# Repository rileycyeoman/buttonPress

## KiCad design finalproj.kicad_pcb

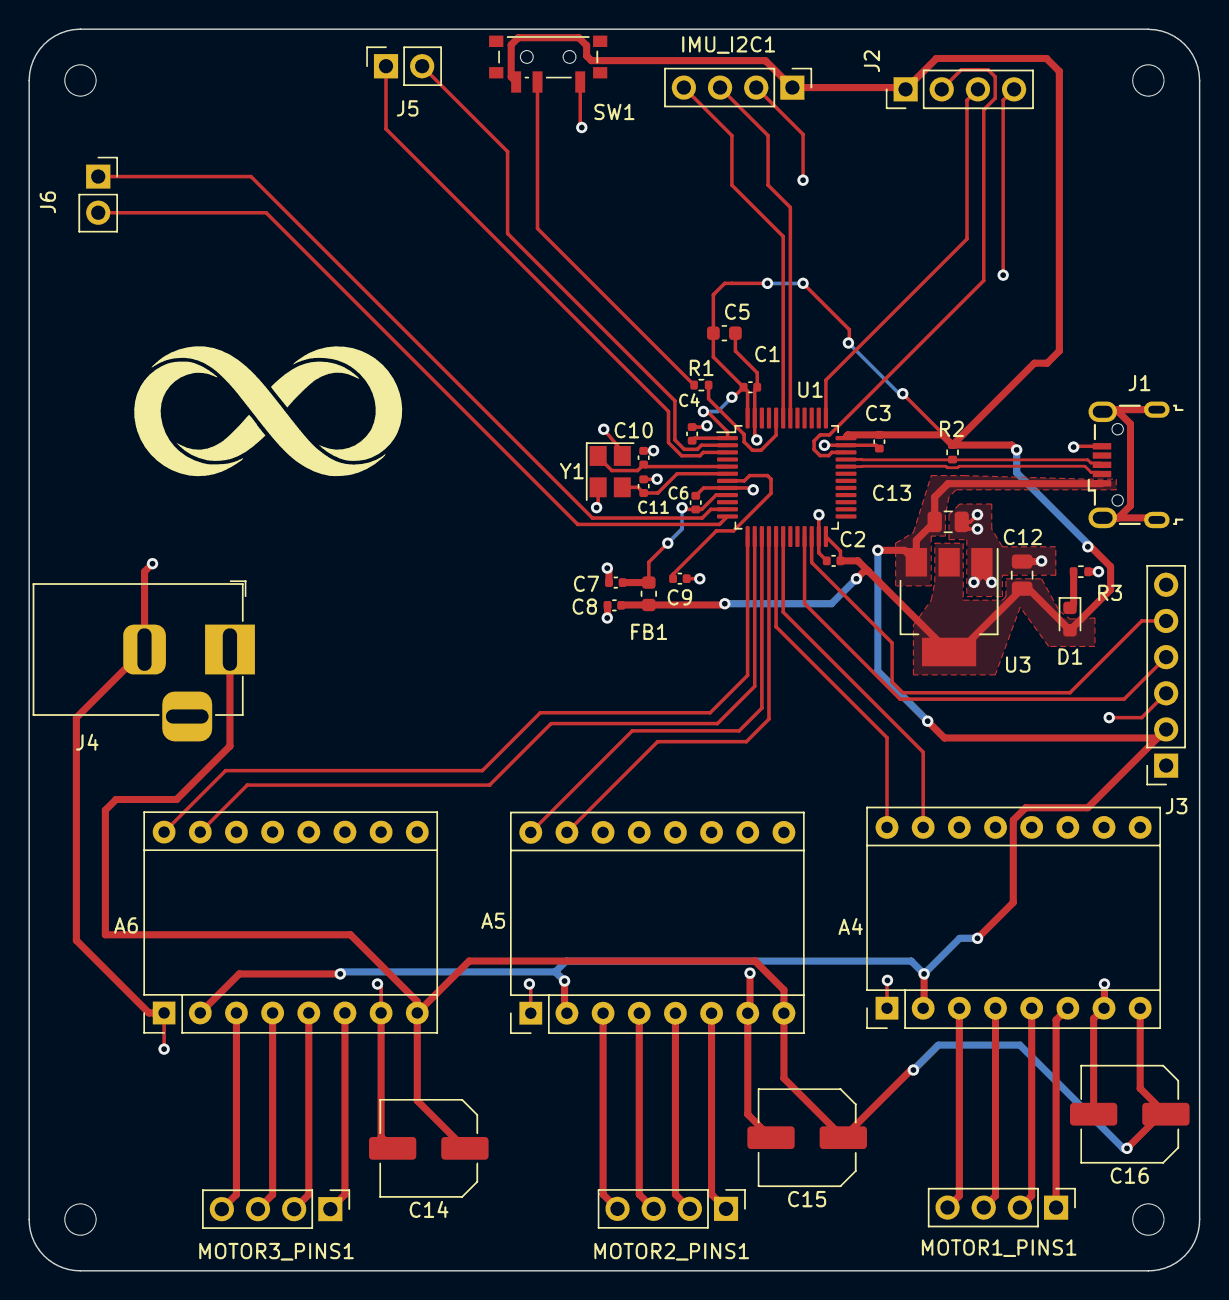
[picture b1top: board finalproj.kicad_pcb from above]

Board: 2 copper layers, 82.2 x 87.2 mm, 43 parts (0 on the bottom side), 41 nets.

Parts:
A4, A5, A6: Pololu_Breakout_A4988; Pololu_Breakout-16_15.2x20.3mm
C1, C2, C3, C4, C9: 100nF; C_0402_1005Metric
C5: 10uF; C_0603_1608Metric
C6: 10nF; C_0402_1005Metric
C7, C8: 1uF; C_0402_1005Metric
C10, C11: 10pF; C_0402_1005Metric
C12, C13: 22uF; C_0805_2012Metric
C14, C15, C16: 47uF; C_Elec_6.3x5.8
D1: LED; LED_0603_1608Metric
FB1: 120R; L_0603_1608Metric
H1, H2, H3, H4: MountingHole; MountingHole_2.2mm_M2
IMU_I2C1: Conn_01x04_Pin; PinHeader_1x04_P2.54mm_Vertical
J1: USB_B_Micro; USB_Micro-B_Wuerth_629105150521
J2: Conn_01x04_Pin; PinHeader_1x04_P2.54mm_Vertical
J3: BLUETOOTH SOCKET; PinSocket_1x06_P2.54mm_Vertical
J4: 12V Input; BarrelJack_Horizontal
J5: GPIO Inputs; PinSocket_1x02_P2.54mm_Vertical
J6: GPIO Outputs; PinSocket_1x02_P2.54mm_Vertical
MOTOR1_PINS1, MOTOR2_PINS1, MOTOR3_PINS1: Conn_01x04_Pin; PinHeader_1x04_P2.54mm_Vertical
R1: 10K; R_0402_1005Metric
R2, R3: 1k5; R_0402_1005Metric
Riley Yeoman: LOGO; evenBetter
SW1: SW_SPDT; SW_SPDT_PCM12
U1: STM32F103C8T6; LQFP-48_7x7mm_P0.5mm
U3: AMS1117-3.3; SOT-223-3_TabPin2
Y1: 16MHz; Crystal_SMD_3225-4Pin_3.2x2.5mm

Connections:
+3.3V: C1.1, C2.1, C3.1, C4.1, C5.1, C8.1, C12.1, D1.2 (A), FB1.2, IMU_I2C1.1, J2.1, R2.2, SW1.3 (C), U1.1 (VBAT), U1.24 (VDD), U1.36 (VDD), U1.48 (VDD), U3.2 (VO)
+3.3VA: C6.1, C7.1, FB1.1, U1.9 (VDDA)
+12V: A4.8 (VMOT), A5.8 (VMOT), A6.8 (VMOT), C14.1, C15.1, C16.1, J4.1
/STM32 Board/BOOT0: R1.2, U1.44 (BOOT0)
/STM32 Board/GPIO_IN1: J5.2, U1.2 (PC13)
/STM32 Board/GPIO_IN2: J5.1, U1.3 (PC14)
/STM32 Board/GPIO_OUT1: J6.1, U1.11 (PA1)
/STM32 Board/GPIO_OUT2: J6.2, U1.12 (PA2)
/STM32 Board/HSE_IN: C10.1, U1.5 (PD0), Y1.1
/STM32 Board/HSE_OUT: C11.1, U1.6 (PD1), Y1.3
/STM32 Board/NSRT: C9.1, U1.7 (NRST)
/STM32 Board/SW_BOOT0: R1.1, SW1.2 (B)
BT_RX: J3.5, U1.22 (PB11)
BT_TX: J3.4, U1.21 (PB10)
DIR M1: A4.16 (DIR), U1.17 (PA7)
DIR M2: A5.16 (DIR), U1.15 (PA5)
DIR M3: A6.16 (DIR), U1.13 (PA3)
GND: A4.1 (GND), A4.7 (GND), A5.1 (GND), A5.7 (GND), A6.1 (GND), A6.7 (GND), C1.2, C2.2, C3.2, C4.2, C5.2, C6.2, C7.2, C8.2, C9.2, C10.2, C11.2, C12.2, C13.2, C14.2, C15.2, C16.2, IMU_I2C1.2, J1.5 (GND), J2.4, J3.3, J4.2, R3.1, SW1.1 (A), U1.8 (VSSA), U1.23 (VSS), U1.35 (VSS), U1.47 (VSS), U3.1 (GND), Y1.2, Y1.4
IMU1_SCL: IMU_I2C1.3, U1.42 (PB6)
IMU1_SDA: IMU_I2C1.4, U1.43 (PB7)
unnamed: A4.4 (1A), MOTOR1_PINS1.3
unnamed: A4.3 (1B), MOTOR1_PINS1.4
unnamed: A4.5 (2A), MOTOR1_PINS1.2
unnamed: A4.6 (2B), MOTOR1_PINS1.1
unnamed: A5.4 (1A), MOTOR2_PINS1.3
unnamed: A5.3 (1B), MOTOR2_PINS1.4
unnamed: A5.5 (2A), MOTOR2_PINS1.2
unnamed: A5.6 (2B), MOTOR2_PINS1.1
unnamed: A6.4 (1A), MOTOR3_PINS1.3
unnamed: A6.3 (1B), MOTOR3_PINS1.4
unnamed: A6.5 (2A), MOTOR3_PINS1.2
unnamed: A6.6 (2B), MOTOR3_PINS1.1
unnamed: D1.1 (K), R3.2
STEP M1: A4.15 (STEP), U1.18 (PB0)
STEP M2: A5.15 (STEP), U1.16 (PA6)
STEP M3: A6.15 (STEP), U1.14 (PA4)
SWCLK: J2.3, U1.37 (PA14)
SWDIO: J2.2, U1.34 (PA13)
USB_D+: J1.3 (D+), R2.1, U1.33 (PA12)
USB_D-: J1.2 (D-), U1.32 (PA11)
VBUS: A4.2 (VDD), A5.2 (VDD), A6.2 (VDD), C13.1, J1.1 (VBUS), J3.2, U3.3 (VI)
